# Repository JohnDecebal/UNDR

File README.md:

# UNDR AUTO: Automatic WDT Tool for Espresso

## Description

UNDR AUTO is a fully automatic WDT (Weiss Distribution Technique) tool designed for espresso enthusiasts. This open-source DIY project combines 3D printed parts with electronic and mechanical components to create a precise and customizable coffee distribution tool. By evenly distributing coffee grounds in the portafilter basket, UNDR AUTO aims to improve the consistency and quality of espresso shots.

## Key Features

- Fully automatic operation with proximity sensor activation
- Adjustable portafilter basket depth
- Variable speed control for vertical movement and distribution
- Customizable distribution patterns with 24 needle slots
- Wi-Fi control via onboard ESP32-S3 webserver
- Compact design with custom UNDR PCB

## Components Overview

The UNDR AUTO utilizes a mix of off-the-shelf and custom components:

- NEMA 17 Stepper Motors for precise movement
- Lead Screw System for vertical adjustment
- Custom 3D printed parts for the main structure
- UNDR PCB with ESP32-S3 for control and connectivity
- Various fasteners and electronic components

For a detailed list, please refer to the Bill of Materials (BOM) in this repository.

## Current Status and Limitations

**Important:** UNDR AUTO is currently in a prototype stage. Potential builders should be aware of the following:

1. Some 3D printed parts may require minor adjustments for proper fit.
2. The current wiring setup is not optimal and requires careful handling.
3. Assembly can be challenging, with some hard-to-reach fastening points.
4. The portafilter mount is specifically designed for Cafe Racer machines and will need modification for other models.
5. There's significant room for improvement in various aspects of the design.

We welcome contributions to address these limitations and enhance the overall design.

## Assembly Guide

Follow these detailed steps to assemble your UNDR AUTO:

1. **3D Printing:**
   - Print all parts listed in the "3D Printed Parts" section of the BOM.
   - Ensure prints are clean and free of defects. Sand parts if necessary for proper fit.
   - Pay special attention to the tolerances of connecting parts.

2. **Prepare the Main Body:**
   - Assemble the four parts of the main body, ensuring they fit snugly together.
   - Install M4 heated inserts into designated holes on the main body. Use a soldering iron to carefully melt the inserts into place.
   - Install 2 heated inserts on the lead screw mount.
   - Apply a strong adhesive to glue the grounds shield holder in place on the body. Ensure proper alignment before the glue sets.

3. **Motor and Lead Screw Installation:**
   - Attach the NEMA 17 stepper motor to the motor mount using M3 screws. Ensure the motor is securely fastened.
   - Install the lead screw system, carefully aligning it with the motor shaft. Use a coupling to connect the motor shaft to the lead screw.

4. **Carriage and Portafilter Mount Assembly:**
   - Install 4 bearings (ID 4mm x OD 8mm x Width 3mm) onto the carriage.
   - Attach the lead screw nut to the carriage using two M3 tapping screws.
   - Connect the portafilter mount to the leadscrew carriage. Note: This connection should be secure but allow for some movement to accommodate different portafilter sizes.

5. **Electronics Installation:**
   - Place the UNDR PCB in the designated space at the bottom of the tool. 
   - Note: The current design doesn't include mounting points for the PCB. Handle with care when moving the assembled unit.
   - Connect the ESP32-S3 to the PCB, ensuring all pins are properly aligned.
   - Install the proximity sensor.

6. **Wiring:**
   - Connect stepper motors to the PCB using the provided cables. Double-check the connections to ensure proper motor direction.
   - Carefully route all wires to avoid interference with moving parts.
   - Use cable ties or electrical tape to secure wires neatly along the frame of the device.

7. **Distributor Assembly:**
   - Assemble the distributor, magnetic connector, lid, arm, and cog.
   - Ensure the distributor spins freely and is properly aligned with the portafilter position.

8. **Lid Assembly:**
   - Assemble the lid using its 4 parts.
   - If desired, install small neodymium magnets in the provided slots for a satisfying close. Ensure polarity is correct for proper attraction to the main body.

9. **Tray Preparation:**
   - Glue magnets in place on the tray and corresponding spots on the body. This allows the tray to snap in place and be easily removed for cleaning.

10. **Final Assembly:**
    - Attach the assembled lid to the main body. Verify that it opens and closes smoothly.
    - Install the bottom lid, securing it with the appropriate screws.
    - Attach the threaded grounds shield to its glued holder, ensuring it's properly aligned with the distributor.

11. **Software Installation:**
    - Connect the ESP32 to your computer using a USB cable.
    - Download the latest firmware from the GitHub repository.
    - Use the Arduino IDE or your preferred ESP32 flashing tool to upload the code to the ESP32.
    - Verify that the upload was successful by checking for any error messages in the IDE.

12. **Testing and Calibration:**
    - Power on the device and connect to its Wi-Fi network (default SSID: "UNDR AUTO").
    - Access the web interface by navigating to 192.168.1.100 in your web browser.
    - Use the interface to test all movements: vertical travel, distribution rotation, and sensor activation.
    - Adjust settings as needed for your specific setup and preferences.

**Important Assembly Tips:**
- Use 90-degree allen wrenches for hard-to-reach fasteners, particularly in the main body assembly.
- Take your time and don't force parts together. If something doesn't fit, double-check the 3D print quality and sand if necessary.
- If using a portafilter other than Cafe Racer, you'll need to modify the mount design. Measure your portafilter carefully and adjust the 3D model accordingly.
- When gluing parts (like magnets or the grounds shield holder), ensure proper alignment before the glue sets.
- When flashing the code, make sure you have the correct board and port selected in your IDE.
- If you encounter any issues during the flashing process, double-check your connections and try resetting the ESP32.

Remember, this is a prototype design and you may encounter challenges during assembly. Don't hesitate to reach out to the community for support or share your improvement ideas!

## Usage Instructions

1. Connect to the UNDR AUTO Wi-Fi network
2. Access the web interface at 192.168.1.100
3. Configure settings (basket depth, speeds, rotation)
4. Place the filled portafilter on the mount
5. The device will automatically start the distribution process
6. Remove the portafilter and tamp as usual

Note: The current version does not support profile saving or live monitoring.

## Customization and Contribution

We strongly encourage users to customize the UNDR AUTO and contribute to its development. Here are some ways you can get involved:

### Customization

1. **Portafilter Mount:**
   - The current design is specific to Cafe Racer machines. We encourage users with different machines to create and share alternative designs.
   - When designing a new mount:
     - Carefully measure your portafilter's dimensions and unique features.
     - Use CAD software to modify the existing design or create a new one.
     - Consider factors like weight distribution and stability.
     - Share your designs with the community to help others with similar machines.

2. **Distribution Patterns:**
   - Experiment with different needle configurations in the 24 available slots.
   - Share your findings on how different patterns affect extraction.

3. **Software Tweaks:**
   - Modify the Arduino code to add new features or optimize existing ones.
   - If you create useful modifications, consider submitting them as pull requests.

### Contributing to the Project

We welcome contributions in various areas:

1. **Hardware Improvements:**
   - Refine the 3D printed parts for better fit and easier assembly.
   - Design solutions for improved wire management.
   - Develop a more secure method for attaching the portafilter mount to the leadscrew carriage.
   - Create a mounting solution for the PCB to prevent movement during operation.

2. **Software Enhancements:**
   - Implement profile saving and loading functionality in the web interface.
   - Add live monitoring capabilities for real-time adjustment during operation.
   - Develop over-the-air (OTA) firmware update functionality.
   - Create a mobile app for easier control and monitoring.

3. **Testing and Quality Assurance:**
   - Develop standardized testing procedures for assembled units.
   - Create a quality checklist for 3D printed parts.
   - Report bugs or suggest improvements based on your experience with the device.

### How to Contribute

1. Fork the repository on GitHub.
2. Create a new branch for your feature or bug fix.
3. Make your changes, ensuring they adhere to the project's coding standards.
4. Test your changes thoroughly.
5. Submit a pull request with a clear description of your changes and their benefits.
6. Engage in any feedback or discussion about your contribution.

### Community Guidelines

- Be respectful and constructive in all interactions.
- When reporting issues, provide as much detail as possible, including steps to reproduce.
- For major changes or new features, open an issue for discussion before submitting a pull request.
- Follow the project's coding style and documentation standards.
- Ensure all contributions are your own work or properly attributed.

Your contributions, no matter how small, are valuable to the project and the entire UNDR AUTO community. Together, we can create an exceptional tool for espresso enthusiasts worldwide!

## License

Copyright 2024 Ionut Decebal, UNDR COFFEE

This project is licensed under the CERN Open Hardware Licence Version 2 - Strongly Reciprocal (CERN-OHL-S v2). You may redistribute and modify this project under the terms specified at https://ohwr.org/cern_ohl_s_v2.txt.

This project is distributed WITHOUT ANY EXPRESS OR IMPLIED WARRANTY, INCLUDING OF MERCHANTABILITY, SATISFACTORY QUALITY AND FITNESS FOR A PARTICULAR PURPOSE. Please see the CERN-OHL-S v2 for applicable conditions.

## Acknowledgments and Contact

- Inspired by WDT techniques discussed on r/espresso
- Thanks to all contributors and testers

For questions or support, contact:
John Decebal - undr.coffee@gmail.com

Project Repository: [https://github.com/JohnDecebal/UNDR](https://github.com/JohnDecebal/UNDR)

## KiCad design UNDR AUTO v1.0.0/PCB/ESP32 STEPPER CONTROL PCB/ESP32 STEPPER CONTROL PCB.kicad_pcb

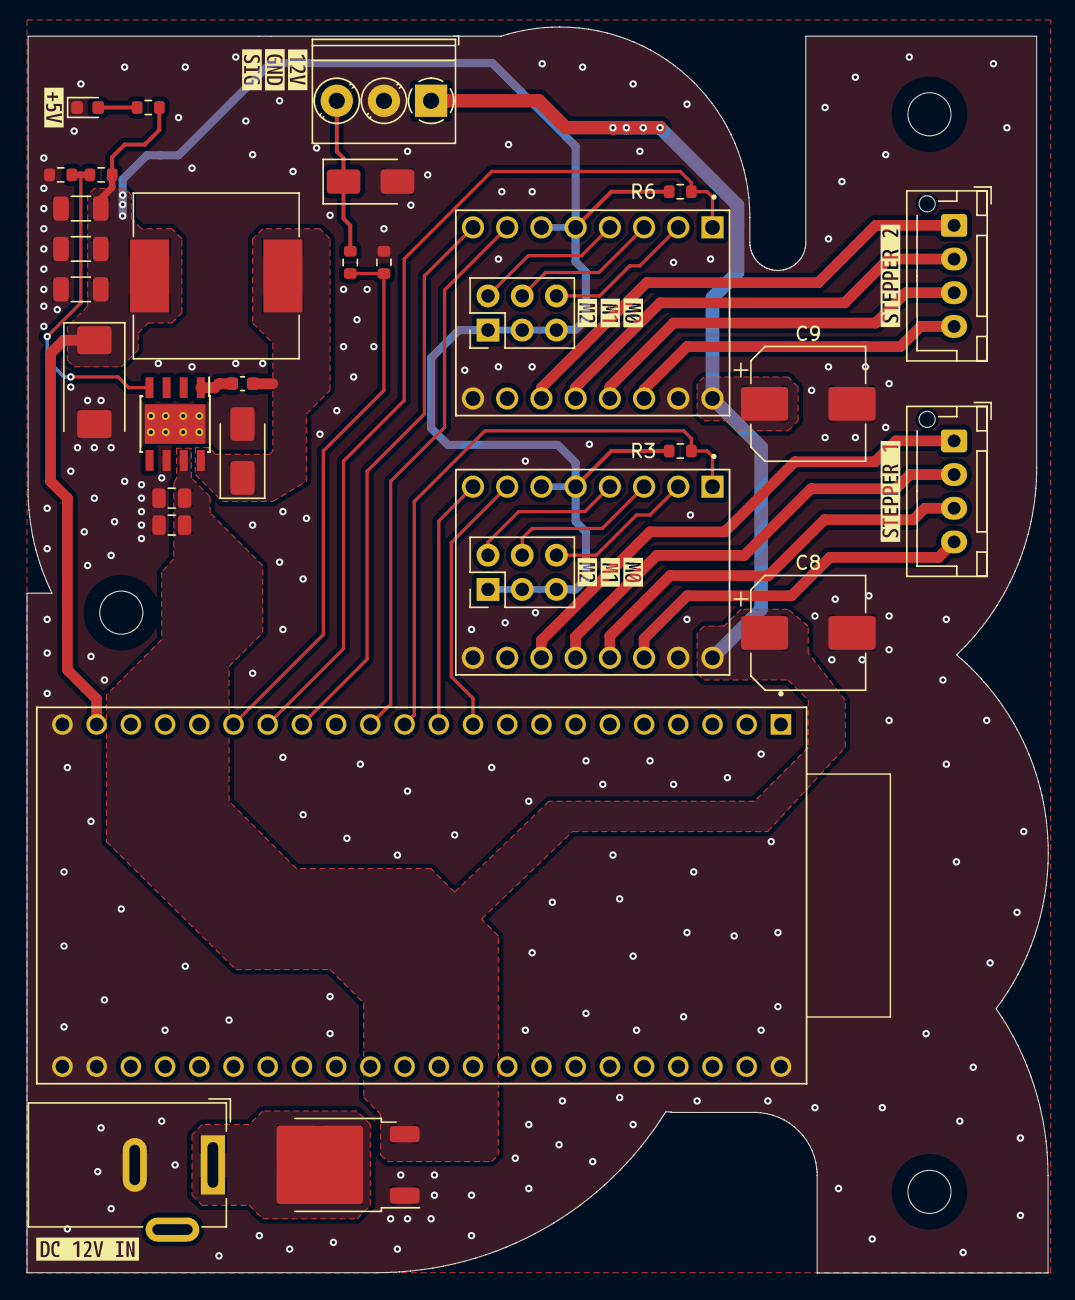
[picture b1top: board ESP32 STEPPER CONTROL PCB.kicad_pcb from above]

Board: 2 copper layers, 75.8 x 92.5 mm, 47 parts (0 on the bottom side), 30 nets.

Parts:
C1: 10nF; C_0603_1608Metric
C2, C3: 2.2uF; C_0805_2012Metric
C4: 220uF; CP_EIA-7343-31_Kemet-D
C5: 22uF; C_1206_3216Metric
C6: 10uF; C_1206_3216Metric
C7: 100nF; C_1206_3216Metric
C8, C9: 100uF; CP_Elec_8x10
D1: B340A; D_SMA
D2: SMAJ12CA-TR; D_SMA
D3: Yellow; LED_0603_1608Metric
H1, H2, H3: MountingHole; MountingHole_3.2mm_M3_DIN965
J1: DC-005-20A; BarrelJack_Wuerth_6941xx301002
J2: Conn_01x03; TerminalBlock_Phoenix_PT-1,5-3-3.5-H_1x03_P3.50mm_Horizontal
J3, J5: Conn_01x04; JST_XH_B4B-XH-AM_1x04_P2.50mm_Vertical
J4, J6: Conn_02x03_Odd_Even; PinHeader_2x03_P2.54mm_Vertical
L1: 22uH; SMDRI127-220MT
Q1: HSU60P03; TO-252-2
R1: 13k; R_0603_1608Metric
R2: 4.12k; R_0603_1608Metric
R3, R6: 10k; R_0603_1608Metric
R4: 56k; R_0603_1608Metric
R5: 18k; R_0603_1608Metric
R7: 330R; R_0603_1608Metric
U1: TPS5430DDA; TI_SO-PowerPAD-8_ThermalVias
U2, U4: DRV8825_STEPPER_MOTOR_DRIVER_CARRIER
U3: ESP32-S3-DEVKIT; ESP32-S3-DEVKITC
kibuzzard-661D4DC0: G***; kibuzzard-661D4DC0
kibuzzard-661D7A6E: G***; kibuzzard-661D7A6E
kibuzzard-661D7A47: G***; kibuzzard-661D7A47
kibuzzard-661D7A91, kibuzzard-661D7A91#2: G***; kibuzzard-661D7A91
kibuzzard-661D7AAA, kibuzzard-661D7AAA#2: G***; kibuzzard-661D7AAA
kibuzzard-661D7AB9, kibuzzard-661D7AB9#2: G***; kibuzzard-661D7AB9
kibuzzard-661D7B73: G***; kibuzzard-661D7B73
kibuzzard-661D7B98: G***; kibuzzard-661D7B98
kibuzzard-661D7BA7: G***; kibuzzard-661D7BA7
kibuzzard-661D68F2: G***; kibuzzard-661D68F2

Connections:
+5V: C4.1, C5.1, C6.1, C7.1, J4.1, J4.3, J4.5, J6.1, J6.3, J6.5, L1.2, R1.1, R3.1, R6.1, R7.1, U2.5 (~RST), U2.6 (~SLP), U3.J1_21 (5V0), U4.5 (~RST), U4.6 (~SLP)
+12V: C2.1, C3.1, C8.1, C9.1, J2.1, Q1.3 (S), U1.7 (VIN), U2.16 (VMOT), U4.16 (VMOT)
/VSENSE: R1.2, R2.1, U1.4 (VSENSE)
GND: C2.2, C3.2, C4.2, C5.2, C6.2, C7.2, C8.2, C9.2, D1.2 (A), D2.2 (A2), D3.1 (K), J1.2, J2.2, Q1.1 (G), R2.2, R5.2, U1.6 (GND), U1.9 (GNDPAD), U2.9 (GND), U2.15 (GND_MOT), U3.J1_22 (GND), U3.J3_1 (GND), U3.J3_21 (GND), U3.J3_22 (GND), U4.9 (GND), U4.15 (GND_MOT)
unnamed: C1.2, D1.1 (K), L1.1, U1.8 (PH)
unnamed: D2.1 (A1), J2.3, R4.1
unnamed: D3.2 (A), R7.2
unnamed: J4.2, U2.4 (M2)
unnamed: J4.4, U2.3 (M1)
unnamed: J4.6, U2.2 (M0)
unnamed: J6.2, U4.4 (M2)
unnamed: J6.4, U4.3 (M1)
unnamed: J6.6, U4.2 (M0)
unnamed: J1.1, Q1.2 (D)
unnamed: C1.1, U1.1 (BOOT)
ProximityOut: R4.2, R5.1, U3.J1_17 (GPIO11)
STEPPER_1_DIR: U2.8 (DIR), U3.J1_11 (GPIO18)
STEPPER_1_EN: R3.2, U2.1 (~EN), U3.J1_12 (GPIO8)
STEPPER_1_STEP: U2.7 (STEP), U3.J1_10 (GPIO17)
STEPPER_2_DIR: U3.J1_15 (GPIO9), U4.8 (DIR)
STEPPER_2_EN: R6.2, U3.J1_16 (GPIO10), U4.1 (~EN)
STEPPER_2_STEP: U3.J1_13 (GPIO3), U4.7 (STEP)
STPR_1_A1: J3.2, U2.12 (A1)
STPR_1_A2: J3.1, U2.11 (A2)
STPR_1_B1: J3.3, U2.13 (B1)
STPR_1_B2: J3.4, U2.14 (B2)
STPR_2_A1: J5.2, U4.12 (A1)
STPR_2_A2: J5.1, U4.11 (A2)
STPR_2_B1: J5.3, U4.13 (B1)
STPR_2_B2: J5.4, U4.14 (B2)

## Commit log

2024-08-04 V1.0.0
2024-08-05 BOM and organising files
2024-08-05 README
2024-09-20 Added STEP files
